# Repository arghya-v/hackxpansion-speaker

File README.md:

# hackxpansion Speaker Module

**Crates:** pkg:cargo/hackxpansion_speaker@0.1.0
<br/>
A speaker module for hackxpansion that allows sound to be emitted from the device

The module takes digital audio from the Hackxpansion controller, converts it to an analog signal, amplifies it, and drives a speaker
## Images

## Schematic

## Overview

The Speaker Module provides the HackXpansion system with a dedicated audio output.

```text
                    Hackxpansion Controller
                              │
                              │
                    ┌─────────┴─────────┐
                    │    Digital Audio  │
                    │                   │
                    └─────────┬─────────┘
                              │
                              ▼
                    ┌───────────────────┐
                    │  TLV320DAC3100    │
                    │    Audio DAC      │
                    └─────────┬─────────┘
                              │
                              │ Analog Audio
                              ▼
                    ┌───────────────────┐
                    │      PAM8320      │
                    │  Class-D Amplifier│
                    └─────────┬─────────┘
                              │
                              ▼
                         ┌─────────┐
                         │ Speaker │
                         └─────────┘
```

The controller sends digital audio to the module over I²S. The TLV320DAC3100 converts the digital signal into analog audio, which is then amplified by the PAM8320 before being sent to the speaker.

## Features
* 48 kHz, 16-bit audio
* Two user-input buttons

## Hardware

The **TLV320DAC3100** converts the incoming digital I²S stream into an analog audio signal.

It is configured for:

```text
Sample Rate: 48 kHz
Bit Depth:   16-bit
Interface:   I²S
MCLK:        12.288 MHz
```

The DAC is controlled over I²C and has a dedicated hardware reset line.

The analog output from the DAC is passed to a **PAM8320 Class-D amplifier**.

## Module Interface

The module uses the HackXpansion GPIO bank for both audio and user input.

| GPIO  | Function  |
| ----- | --------- |
| GPIO0 | I²C SCL   |
| GPIO1 | I²C SDA   |
| GPIO2 | I²S BCLK  |
| GPIO3 | I²S DIN   |
| GPIO4 | I²S LRCLK |
| GPIO5 | MCLK      |
| GPIO6 | DAC RESET |
| GPIO7 | Button 1  |
| GPIO8 | Button 2  |
| GPIO9 | Unused    |

See the [Xpanse API docs](https://docs.rs/xpanse-api/latest/xpanse_api/index.html)

This allows the main HackXpansion firmware to assign functionality to the buttons without the speaker module needing to know what those actions are.

The driver is responsible for:

1. Resetting the audio DAC
2. Configuring the DAC over I²C
3. Starting the master clock
4. Starting the I²S output
5. Registering the audio interface with HackXpansion
6. Registering the module buttons

`lib.rs` contains the HackXpansion-specific module driver, while `dac.rs` contains the reusable TLV320DAC3100 driver.

---

This was all possible thanks to [Hackspansion: A hackclub YSWS](http://hackxpansion.hackclub.com/)

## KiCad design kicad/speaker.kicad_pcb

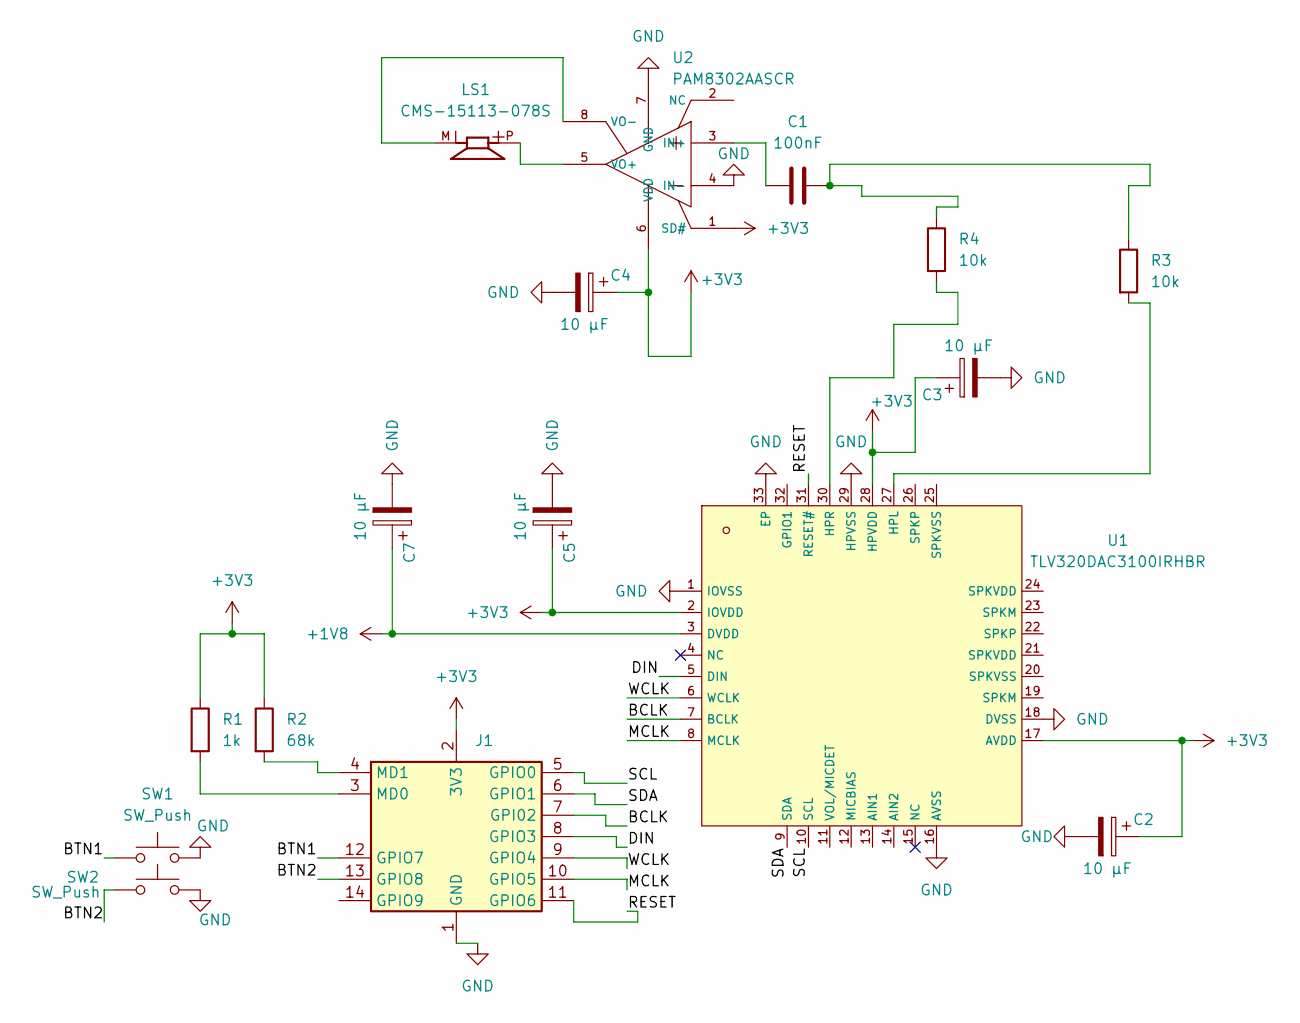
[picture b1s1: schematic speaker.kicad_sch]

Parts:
C1: 100nF; C155422_C0402
C2, C3, C4, C5, C7: 10 µF; C15850_C0805
J1: Male_Module
LS1: CMS-15113-078S; SPKR_CMS-15113-078S; PARTREV 1
R1: 1k; R_0805_2012Metric_Pad1.20x1.40mm_HandSolder
R2: 68k; R_0805_2012Metric_Pad1.20x1.40mm_HandSolder
R3, R4: 10k; R_0805_2012Metric_Pad1.20x1.40mm_HandSolder
SW1, SW2: SW_Push; SW_PUSH_6mm
U1: TLV320DAC3100IRHBR; C179677_LFCSP-32_L5_0-W5_0-P0_50-BL-EP; LCSC C179677
U2: PAM8302AASCR; C113367_MSOP-8_L3_0-W3_0-P0_65-LS5_0-BL; LCSC C113367

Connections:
+1V8: C7.1, U1.3 (DVDD)
+3V3: C2.1, C3.1, C4.1, C5.1, J1.2 (3V3), R1.1, R2.1, U1.2 (IOVDD), U1.17 (AVDD), U1.28 (HPVDD), U2.1 (SD#), U2.6 (VDD)
/BCLK: J1.7 (GPI02), U1.7 (BCLK)
/BTN1: J1.12 (GPIO7), SW1.1
/BTN2: J1.13 (GPIO8), SW2.1
/DIN: J1.8 (GPIO3), U1.5 (DIN)
/MCLK: J1.10 (GPIO5), U1.8 (MCLK)
/RESET: J1.11 (GPIO6), U1.31 (RESET#)
/SCL: J1.5 (GPIO0), U1.10 (SCL)
/SDA: J1.6 (GPIO1), U1.9 (SDA)
/WCLK: J1.9 (GPIO4), U1.6 (WCLK)
GND: C2.2, C3.2, C4.2, C5.2, C7.2, J1.1 (GND), SW1.2, SW2.2, U1.1 (IOVSS), U1.16 (AVSS), U1.18 (DVSS), U1.29 (HPVSS), U1.33 (EP), U2.4 (IN-), U2.7 (GND)
unnamed: C1.2, R3.1, R4.1
unnamed: J1.3 (MD0), R1.2
unnamed: J1.4 (MD1), R2.2
unnamed: R3.2, U1.27 (HPL)
unnamed: R4.2, U1.30 (HPR)
unnamed: C1.1, U2.3 (IN+)
unnamed: LS1.P, U2.5 (VO+)
unnamed: LS1.M, U2.8 (VO-)

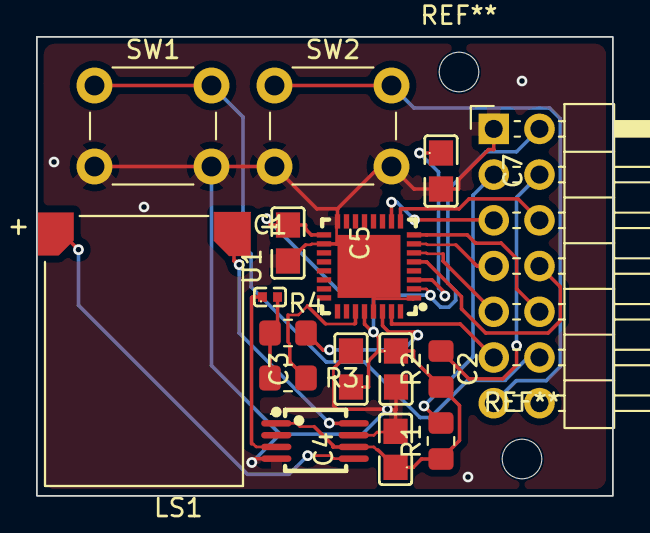
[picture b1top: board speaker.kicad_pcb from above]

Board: 2 copper layers, 32.0 x 25.5 mm, 16 parts (0 on the bottom side), 20 nets.

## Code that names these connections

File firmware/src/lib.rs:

#![no_std]

pub mod dac;

use embassy_rp::{
    dma,
    gpio::{Level, Output},
    interrupt::typelevel::{Binding, DMA_IRQ_0},
    peripherals::DMA_CH0,
    pio_programs::{
        clk::{PioClk, PioClkProgram},
        i2s::{PioI2sOut, PioI2sOutProgram},
    },
};

use xpanse_api::{
    with_pio,
    bus::allocator::BusAllocator,
    driver::{Driver, DriverError, DriverMeta},
    gpio_bank::{BankPins, GpioBank},
    interfaces::buttons::{
        pin_button,
        A,
        B,
    },
    metadata::{
        ModuleDetectResistor,
        ModuleID,
        ModuleSlot,
    },
    registry::Registry,
};

const SAMPLE_RATE: u32 = 48_000;
const BIT_DEPTH: u32 = 16;
const MCLK_FREQUENCY: u32 = 12_288_000;

#[derive(Copy, Clone)]
pub struct AudioDmaIrqs;

unsafe impl Binding<DMA_IRQ_0, dma::InterruptHandler<DMA_CH0>> for AudioDmaIrqs {}

pub struct SpeakerDriver;

impl DriverMeta for SpeakerDriver {
    const ID: ModuleID = ModuleID {
        md0: ModuleDetectResistor::R1K,
        md1: ModuleDetectResistor::R68K,
    };
}

impl<G> Driver<G> for SpeakerDriver
where
    G: BankPins,
{
    async fn create(
        bank: GpioBank<G>,
        slot: ModuleSlot,
        registry: &mut Registry,
        buses: &mut BusAllocator,
    ) -> Result<(), DriverError> {

        let mut reset = Output::new(
            bank.gpio6,
            Level::Low,
        );

        embassy_time::Timer::after_millis(5).await;

        reset.set_high();

        embassy_time::Timer::after_millis(10).await;

        core::mem::forget(reset);

        let mut i2c_bus = buses
            .create_i2c_bitbang(
                bank.gpio0,
                bank.gpio1,
                400_000,
            )
            .map_err(|_| DriverError::InitFailed)?;

        dac::reset(&mut i2c_bus).await?;

        dac::configure(&mut i2c_bus).await?;

        registry.register(
            slot,
            Self::ID,
            pin_button::<A>(
                bank.gpio7.into(),
            ),
        );

        registry.register(
            slot,
            Self::ID,
            pin_button::<B>(
                bank.gpio8.into(),
            ),
        );

        let dma = buses
            .request_dma::<DMA_CH0>()
            .map_err(|_| DriverError::InitFailed)?;

        let mclk_pio = buses
            .request_pio(&[
                &bank.gpio5,
            ])
            .ok_or(DriverError::InitFailed)?;

        with_pio!(
            mclk_pio,
            mclk_common,
            mclk_sm,
            {
                let mclk_program = PioClkProgram::new(
                    &mut *mclk_common,
                );

                let mut mclk = PioClk::new(
                    &mut *mclk_common,
                    mclk_sm,
                    bank.gpio5,
                    &mclk_program,
                    MCLK_FREQUENCY,
                );

                mclk.start();

                core::mem::forget(mclk);
            }
        );

        let i2s_pio = buses
            .request_pio(&[
                &bank.gpio2,
                &bank.gpio3,
                &bank.gpio4,
            ])
            .ok_or(DriverError::InitFailed)?;

        with_pio!(
            i2s_pio,
            i2s_common,
            i2s_sm,
            {
                let i2s_program = PioI2sOutProgram::new(
                    &mut *i2s_common,
                );

                let mut i2s = PioI2sOut::new(
                    &mut *i2s_common,
                    i2s_sm,
                    dma,
                    AudioDmaIrqs,
                    bank.gpio3,
                    bank.gpio2,
                    bank.gpio4,
                    SAMPLE_RATE,
                    BIT_DEPTH,
                    &i2s_program,
                );

                i2s.start();

                registry.register(
                    slot,
                    Self::ID,
                    i2s,
                );
            }
        );

        Ok(())
    }
}
